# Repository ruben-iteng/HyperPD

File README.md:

<div align="center">

# HyperPD

<br/>

HyperHDR LED controller with USB-PD power input 

</div>

## About

HyperPD is a HyperHDR compatible LED controller with USB-PD as power source. By using XT30 connectors with 2 additional data pins, you can use pre-assembled cables that you only need to solder to your LED strip! All these features make this a very compact and easy to connect solution.

### Features

- USB-C PD power input (15V and 20V)
- 5V @ 8A continuous output for the LEDs
- XT30(2x2) connectors for easy connection to the LED strips
- Support for SPI and WS2812/SK6812 LED strips
- Support for multi-segment LED strip setups
- 100% compatible with HyperSerialPico firmware

## Making your own

Buy the following components:

- Raspberry Pi Pico (or pin compatible board)
- USB-C PD Power Supply
  - This board supports 15V and 20V power input
  - Match the wattage with your LED strip, higher wattage is okay/better
- 1 or 2 [XT30 cables](https://www.aliexpress.com/item/1005007527109751.html)
- The HyperPD board (order the assembled board on JLCPCB or make your own)
- 3D printed case (optional, see [here](./mechanical/README.md))

## Firmware

Firmware informationcan be found [here](./firmware/README.md).

## Mechanical

Files for a 3D printable case can be found [here](./mechanical/README.md).

## Development

Setup atopile:

- Guide can be found [here](https://docs.atopile.io/).

Build the project:

```bash
# In the root of the project
# Using uv to install the dependencies
uv sync
uv run pip install -e .
# Local install is needed for local fabll module imports
```

Build the project default target to generate release artifacts (Gerber, STEP, BOM, P&P,etc.):
```bash
# In the root of the project
atopile build
```

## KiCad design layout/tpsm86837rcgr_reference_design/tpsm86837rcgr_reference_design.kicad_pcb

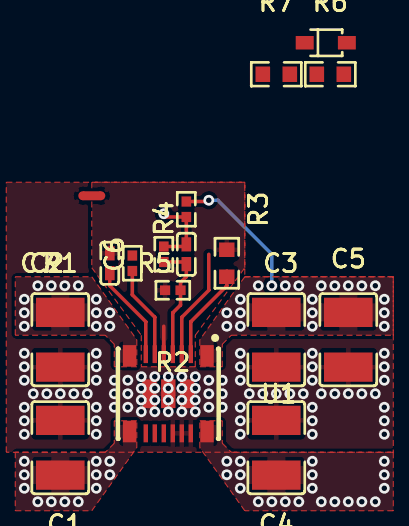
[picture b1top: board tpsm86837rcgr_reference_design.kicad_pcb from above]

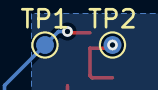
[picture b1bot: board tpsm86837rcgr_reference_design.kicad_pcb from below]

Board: 2 copper layers, 19 parts (2 on the bottom side), 12 nets.

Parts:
C1, C2: 10µF ±10% 35V X7R; C1210-c93926
C3, C4, C5: 22µF ±10% 25V X7R; C1210-c93926
C6: 47pF ±5% 50V C0G; C0402-b3ef17
C7: 22nF ±10% 50V X7R; C0402-b3ef17
D1: SOD-323_L1.8-W1.3-LS2.5-RD-b55baa
JP1: NetTie-2_SMD_Pad0.5mm
R1: 100kΩ ±1% 62.5mW; R0402-56259e
R2, R4: 10kΩ ±1% 62.5mW; R0402-56259e
R3: 49.9Ω ±1% 62.5mW; R0402-56259e
R5, R7: 10kΩ ±1% 100mW; R0603-ebcab9
R6: 1kΩ ±1% 100mW; R0603-ebcab9
TP1, TP2: TestPoint_Pad_D1.0mm
U1: B3QFN-19_L5.5-W5.0-P0.50-TL-114622

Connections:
frequency_mode: R5.1, U1.2
gnd: C1.2, C2.2, C3.2, C4.2, C5.2, D1.2, JP1.1, R6.2, U1.13, U1.14, U1.15, U1.17, U1.18, U1.19
gnd-1: C7.2, JP1.2, R2.2, R5.2, U1.5
hv: C3.1, C4.1, C5.1, U1.1, U1.16
hv-2: C1.1, C2.1, R7.1, U1.8, U1.9
line: D1.1, R6.1, R7.2, U1.3
line-1: R1.1, U1.6
line-2: C6.1, R2.1, R4.2, U1.4
output_voltage_feedback-contact: C6.2, R3.2, R4.1, TP2.1
output_voltage_feedback-contact-1: R3.1, TP1.1
soft_start: C7.1, U1.7
switching_node: U1.10, U1.11

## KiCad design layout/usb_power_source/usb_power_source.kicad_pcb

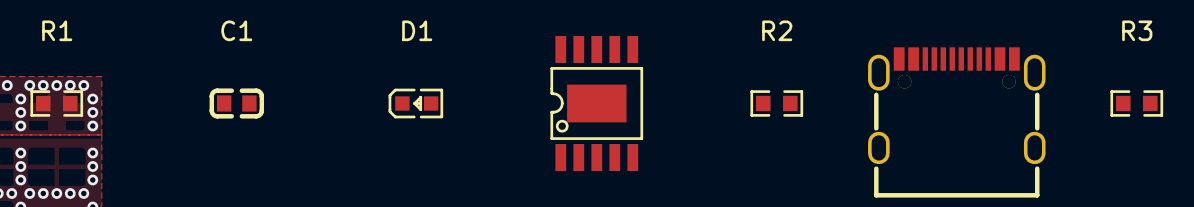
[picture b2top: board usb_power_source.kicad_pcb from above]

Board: 2 copper layers, 7 parts (0 on the bottom side), 11 nets.

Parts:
C1: 1µF ±10% 50V X5R; C0603-bd72f6
D1: LED0603-RD-YELLOW-5af84a
J1: USB-C_SMD-TYPE-C-31-M-12-8412ae
R1, R2: 10kΩ ±1% 100mW; R0603-ebcab9
R3: 1kΩ ±1% 100mW; R0603-ebcab9
U1: ESSOP-10_L4.9-W3.9-P1.0-LS6.0-TL-EP-20a8ca

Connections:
cathode: D1.1, R1.1
cc[0]: J1.A5, U1.7
cc[1]: J1.B5, U1.6
gnd: C1.2, J1.A1, J1.A12, J1.B1, J1.B12, U1.11
gnd-1: R1.2, U1.10
hv: D1.2, J1.A4, J1.A9, J1.B4, J1.B9, R2.2, R3.2
line: J1.A6, J1.B6, U1.4
line-1: J1.A7, J1.B7, U1.5
shield: J1.0, J1.1, J1.2, J1.3
usb_pr_trigger-hv: C1.1, R3.1, U1.1
usb_pr_trigger-line: R2.1, U1.8

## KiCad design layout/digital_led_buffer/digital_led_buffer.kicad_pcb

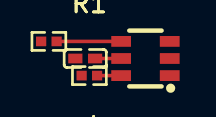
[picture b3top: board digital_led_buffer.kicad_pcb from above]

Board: 2 copper layers, 4 parts (0 on the bottom side), 4 nets.

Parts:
C1: 100nF ±10% 16V X7R; C0402-b3ef17
R1, R2: 470Ω ±1% 62.5mW; R0402-56259e
U1: SOT-23-6_L2.9-W1.6-P0.95-LS2.8-BR-bfc73b

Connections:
gnd: C1.2, U1.2
hv: C1.1, U1.5
line-1: R1.2, U1.6
line-2: R2.2, U1.4

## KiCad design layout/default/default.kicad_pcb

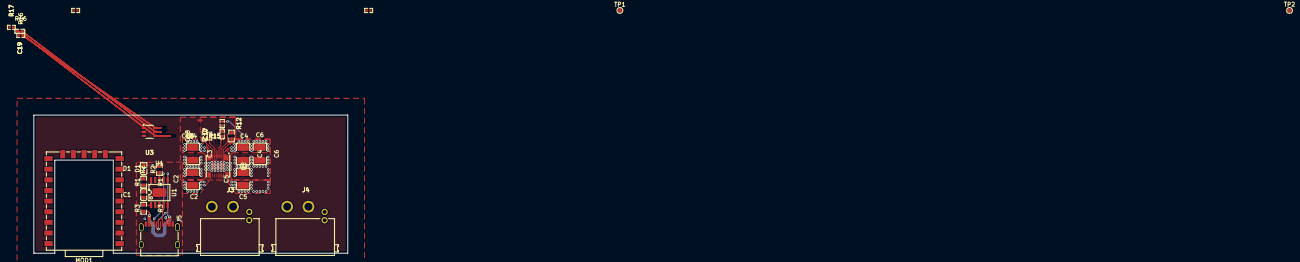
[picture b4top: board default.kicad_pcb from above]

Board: 2 copper layers, 30 parts (0 on the bottom side), 25 nets.

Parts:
C1: 1µF ±10% 50V X5R; C0603-bd72f6
C2, C3: 10µF ±10% 35V X7R; C1210-c93926
C4, C5, C6: 22µF ±10% 25V X7R; C1210-c93926
C17: 47pF ±5% 50V C0G; C0402-b3ef17
C18: 22nF ±10% 50V X7R; C0402-b3ef17
C19: 100nF ±10% 16V X7R; C0402-b3ef17
D1: LED0603-RD-YELLOW-5af84a
J3, J4: CONN-TH_4P-XT30PW-M-e6a65c
J5: USB-C_SMD-TYPE-C-31-M-12-8412ae
JP1: NetTie-2_SMD_Pad0.5mm
MOD1: COMM-SMD_RP2040-ZERO-70d39b
R1, R2: 10kΩ ±1% 100mW; R0603-ebcab9
R3: 1kΩ ±1% 100mW; R0603-ebcab9
R4: 100kΩ ±1% 62.5mW; R0402-56259e
R5, R6: 10kΩ ±1% 62.5mW; R0402-56259e
R12: 49.9Ω ±1% 62.5mW; R0402-56259e
R15: 162kΩ ±1% 100mW; R0603-ebcab9
R16, R17: 470Ω ±1% 62.5mW; R0402-56259e
TP1, TP2: TestPoint_Pad_D1.0mm
U1: ESSOP-10_L4.9-W3.9-P1.0-LS6.0-TL-EP-20a8ca
U2: B3QFN-19_L5.5-W5.0-P0.50-TL-114622
U3: SOT-23-6_L2.9-W1.6-P0.95-LS2.8-BR-bfc73b

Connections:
cathode: D1.1, R1.1
cc[0]: J5.A5, U1.7
cc[1]: J5.B5, U1.6
clock: J3.4, J4.4, R17.1
data: J3.3, J4.3, R16.1
dcdc_module-gnd: C18.2, JP1.2, R5.2, R15.2, U2.5
dcdc_module-line: C17.1, R5.1, R6.2, U2.4
dcdc_module-line-2: R4.1, U2.6
dcdc_module.output_voltage_feedback-contact: C17.2, R6.1, R12.2, TP2.1
dcdc_module.output_voltage_feedback-contact-1: R12.1, TP1.1
frequency_mode: R15.1, U2.2
gnd: C1.2, C2.2, C3.2, C4.2, C5.2, C6.2, C19.2, J3.2, J4.2, J5.A1, J5.A12, J5.B1, J5.B12, JP1.1, MOD1.22, U1.11, U2.13, U2.14, U2.15, U2.17, U2.18, U2.19, U3.2
hv-2: C4.1, C5.1, C6.1, C19.1, U2.1, U2.16, U3.5
led_buffer-line: R17.2, U3.4
led_buffer-line-1: R16.2, U3.6
line: MOD1.4, U3.1
line-1: MOD1.3, U3.3
pd_power_supply-gnd: R1.2, U1.10
pd_power_supply-line: J5.A6, J5.B6, U1.4
pd_power_supply-line-1: J5.A7, J5.B7, U1.5
pd_power_supply.usb_pr_trigger-hv: C1.1, R3.1, U1.1
pd_power_supply.usb_pr_trigger-line: R2.1, U1.8
shield: J5.0, J5.1, J5.2, J5.3
soft_start: C18.1, U2.7
vbus: C2.1, C3.1, D1.2, J5.A4, J5.A9, J5.B4, J5.B9, R2.2, R3.2, U2.8, U2.9

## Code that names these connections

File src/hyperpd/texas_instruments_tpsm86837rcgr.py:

# This file is part of the faebryk project
# SPDX-License-Identifier: MIT

import logging

from atopile.errors import UserNotImplementedError
import faebryk.library._F as F  # noqa: F401
from faebryk.core.module import Module
from faebryk.libs.library import L  # noqa: F401
from faebryk.libs.units import P  # noqa: F401
from faebryk.libs.picker.picker import DescriptiveProperties
from faebryk.libs.util import assert_once

logger = logging.getLogger(__name__)


class TEXAS_INSTRUMENTS_TPSM86837RCGR(Module):
    """
    Power Management Modules 4.5V to 28V input voltage, 8A ECO mode,
    synchronous buck module with QFN package
    """

    # ----------------------------------------
    #               modules
    # ----------------------------------------

    # ----------------------------------------
    #              interfaces
    # ----------------------------------------
    power_out = L.d_field(lambda: F.ElectricPower().make_source())  # pins: 1, 16
    frequency_mode: F.Electrical  # pin: 2
    enable: F.EnablePin  # pin: 3
    feedback: F.ElectricSignal  # pin: 4
    power_analog: F.ElectricPower  # pin: 5
    power_good: F.ElectricLogic  # pin: 6
    soft_start: F.Electrical  # pin: 7
    power_in: F.ElectricPower  # pins: 8, 9
    switching_node: F.Electrical  # pins: 10, 11
    """
    Do not connect, only for better thermal dissipation and reduced parasitic impedance.
    """
    # n.c. bootstrap: F.Electrical  # pin: 12
    # power_ground: F.Electrical  # pins: 17, 18, 19

    # ----------------------------------------
    #               parameters
    # ----------------------------------------
    output_voltage = L.p_field(
        units=P.V,
        likely_constrained=True,
        soft_set=L.Range(0.6 * P.V, 5.5 * P.V),
    )
    switching_frequency = L.p_field(
        units=P.kHz,
        likely_constrained=True,
        soft_set=L.DiscreteSet(800 * P.kHz, 1200 * P.kHz),
    )
    soft_start_time = L.p_field(
        units=P.ms,
        likely_constrained=True,
        soft_set=L.Range(0 * P.ms, 1000 * P.ms),
    )
    # under_voltage_lockout = L.p_field(units=P.V)

    # ----------------------------------------
    #                 traits
    # ----------------------------------------
    designator_prefix = L.f_field(F.has_designator_prefix)(
        F.has_designator_prefix.Prefix.U
    )
    descriptive_properties = L.f_field(F.has_descriptive_properties_defined)(
        {
            DescriptiveProperties.manufacturer: "TEXAS INSTRUMENTS",
            DescriptiveProperties.partno: "TPSM86837RCGR",
        }
    )
    datasheet = L.f_field(F.has_datasheet_defined)(
        "https://www.ti.com/lit/ds/symlink/tpsm86838.pdf"
    )

    @L.rt_field
    def bridge(self):
        return F.can_bridge_defined(self.power_in, self.power_out)

    # TODO: fix, don't connect analog power to ground
    # @L.rt_field
    # def single_electric_reference(self):
    #    return F.has_single_electric_reference_defined(
    #        F.ElectricLogic.connect_all_module_references(self, exclude=self.analog_power,gnd_only=True)
    #    )

    @L.rt_field
    def attach_via_pinmap(self):
        return F.can_attach_to_footprint_via_pinmap(
            {
                "1": self.power_out.hv,
                "2": self.frequency_mode,
                "3": self.enable.enable.line,
                "4": self.feedback.line,
                "5": self.power_analog.lv,
                "6": self.power_good.line,
                "7": self.soft_start,
                "8": self.power_in.hv,
                "9": self.power_in.hv,
                "10": self.switching_node,
                "11": self.switching_node,
                "12": None,  # self.bootstrap,
                "13": self.power_in.lv,
                "14": self.power_in.lv,
                "15": self.power_in.lv,
                "16": self.power_out.hv,
                "17": self.power_in.lv,
                "18": self.power_in.lv,
                "19": self.power_in.lv,
            }
        )

    def __preinit__(self):
        # ------------------------------------
        #           connections
        # ------------------------------------

        # ------------------------------------
        #          parametrization
        # ------------------------------------
        self.power_in.voltage.constrain_subset(L.Range(4.5 * P.V, 28 * P.V))
        self.power_out.voltage.constrain_subset(self.output_voltage)

        # TODO: sofset is currently not used so constrain manually
        self.power_out.voltage.constrain_subset(L.Range(0.6 * P.V, 5.5 * P.V))
        self.switching_frequency.constrain_subset(
            L.DiscreteSet(800 * P.kHz, 1200 * P.kHz)
        )
        self.soft_start_time.constrain_subset(L.Range(0 * P.ms, 1000 * P.ms))

        # The datasheet does not specify a specific voltage, but there is an image of
        # the internal circuitry showing a 5V rail
        # self.power_analog.voltage.constrain_subset(
        #    L.Range.from_center_rel(5 * P.V, 10 * P.percent)
        # ) TODO: unsolvable ...

        # The datasheet does not specify a specific current, 60uA is calculated from
        # the recommended component values in the datasheet (Table 7-2)
        self.feedback.reference.max_current.constrain_subset(
            L.Range.from_center_rel(60 * P.uA, 10 * P.percent)
        )

        # TODO: no support for high/low/hysteresis/min/max voltage for ElectricLogic
        # self.enable.has_single_electric_reference.reference.voltage.constrain_subset(
        #    L.Range(0.5 * P.V, 5.5 * P.V)
        # )

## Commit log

2025-01-03 Add pico footprint submodule
2025-01-10 Make v0.3.x compatible
2025-01-24 Split into modules, and add first layout
2025-01-28 Change PCB layout
2025-01-28 Experiment with converting to solver only parameters
    Add more documentation
2025-01-30 Update to latest ato
2025-02-25 Add project requirements
2025-02-25 Add LED buffer, change DCDC func to params, layout
2025-03-08 Update dcdc modules
2025-03-08 Use rp2040zero module
2025-03-08 Add missing LED connector
    Use different buffer
2025-03-08 Add pcb files
2025-03-14 Restructure project
    Add documentaion
    Fix Reference design
2025-03-14 Connect SW pins to eachother for better performance
    From: https://e2e.ti.com/support/power-management-group/power-management/f/power-management-forum/1433607/tpsm86838-do-the-sw-pins-need-to-be-connected-to-each-other-tpsm86838-and-tpsm86638?tisearch=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
2025-03-14 Clean up module
2025-03-15 Make UVLO compile
2025-03-15 Update ci workflow
2025-03-15 Install project with uv
2025-03-15 update uv lock
2025-03-17 Change uv version to fix minor version bug
2025-03-17 Use explicit python version and venv
2025-03-17 Disable cache

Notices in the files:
README.md:
License: MIT
